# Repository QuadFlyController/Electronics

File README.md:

# QuadFlyController - Flight Controller Hardware

A high-performance, compact, 4-layer flight controller PCB engineered for quadcopters and small UAVs. Built around the STMicroelectronics STM32F411CEU6 MCU, featuring high-rate low-noise motion sensing, barometric altitude tracking, robust power management with dual-source automatic switching, and standard 30.5 mm × 30.5 mm mounting.

---

## 🚀 Key Specifications

| Subsystem | Component | Description |
| :--- | :--- | :--- |
| **Microcontroller (MCU)** | **STM32F411CEU6** | ARM Cortex-M4 @ 100 MHz, FPU, 512 KB Flash, 128 KB SRAM, external 25 MHz HSE oscillator |
| **Inertial Measurement (IMU)** | **ICM-42688-P** | High-precision 6-axis gyroscope & accelerometer on dedicated high-speed SPI bus with interrupt line |
| **Barometer / Altimeter** | **BMP390** | Ultra-low noise barometric pressure sensor on SPI bus for altitude hold |
| **Switching Regulator (Buck)** | **TPS62933** | High-efficiency 3A synchronous step-down converter providing stable +5V rail from battery |
| **Linear Regulator (LDO)** | **AP2112K-3.3** | Ultra-low dropout, low-noise 600 mA 3.3V LDO for clean MCU and analog sensor rails |
| **Power Path Switching** | **TPS2115A** | Seamless automatic power multiplexer between USB VBUS (+5V) and internal Buck converter (+5V) |
| **Transient Protection** | **SMBJ18A** | Bidirectional TVS diode protection on battery input |
| **USB Protection** | **USBLC6-2SC6** | Ultra-low capacitance ESD protection array on USB D+/D- lines |
| **USB Interface** | **USB Type-C (16-pin)** | Firmware flashing (DFU), telemetry, and configuration interface |
| **ESC Interface** | **JST-SH 8-Pin (1.0 mm)** | Standard 4-in-1 ESC connector (VBAT, GND, Motors 1–4, Current sensing) |

---

## 📐 PCB & Mechanical Specifications

- **Dimensions:** 45.0 mm × 45.0 mm with 3.5 mm corner radius
- **Mounting Hole Pattern:** Standard **30.5 mm × 30.5 mm**, 4.3 mm holes (M4, compatible with anti-vibration silicone grommets down to M3 hardware)
- **Layer Stack:** **4-Layer PCB**
  - **F.Cu (Top Layer):** High-speed signals, component breakout, top ground pour
  - **In1.Cu (Inner Layer 1):** Solid ground reference plane (GND)
  - **In2.Cu (Inner Layer 2):** Power distribution (+5V, +3.3V, +BATT) and cross-layer routing
  - **B.Cu (Bottom Layer):** Bottom ground plane and secondary signal routing
- **3D Mechanical Model:** Full 3D STEP model available in [`FlightController/CAD/FlightController.step`](FlightController/CAD/FlightController.step) for frame integration and enclosure design.

---

## 🔌 Pinout & Connector Definitions

### J3: 8-Pin JST-SH 4-in-1 ESC Connector (`SM08B-SRSS-TB`)

| Pin | Net Name | Function / Description |
| :---: | :--- | :--- |
| **1** | `+BATT` | Raw battery voltage input from ESC / PDB |
| **2** | `GND` | Power and signal ground return |
| **3** | `CUR` | Analog current sensing signal from ESC shunt sensor |
| **4** | `M1` | Motor 1 PWM / DShot signal output (STM32 Timer channel) |
| **5** | `M2` | Motor 2 PWM / DShot signal output (STM32 Timer channel) |
| **6** | `M3` | Motor 3 PWM / DShot signal output (STM32 Timer channel) |
| **7** | `M4` | Motor 4 PWM / DShot signal output (STM32 Timer channel) |
| **8** | `GND` | Ground return |

### External Pads & Test Points

- **UART (TX / RX):** External receiver connection (ELRS, Crossfire, SBUS) or GPS telemetry module.
- **SWD (SWDIO / SWCLK):** Hardware debug and in-circuit flashing with ST-Link or J-Link.
- **BOOT0:** Jumper/pad for STM32 internal ROM system bootloader (DFU mode over USB).
- **Status LEDs:**
  - `D1`: Power indicator
  - `D2`: User / Status LED (connected to STM32 GPIO)

---

## 📂 Repository Structure

```text
Electronics/
├── .gitignore                                 # Git ignore configuration
├── LICENSE                                    # License file
├── README.md                                  # Hardware documentation
├── FlightController_Schematic.pdf             # Exported full schematic PDF
│
└── FlightController/                          # KiCad 10 Project Directory
    ├── FlightController.kicad_pro             # KiCad project file
    ├── FlightController.kicad_pcb             # KiCad 4-layer PCB layout
    ├── FlightController.kicad_sch             # Root schematic sheet
    ├── MCU.kicad_sch                          # STM32F411CEU6 microcontroller sheet
    ├── IMU.kicad_sch                          # ICM-42688-P & BMP390 sensor sheet
    ├── PowerManagement.kicad_sch              # Power rails, buck, LDO, & USB sheet
    ├── fp-lib-table                           # Footprint library table
    ├── sym-lib-table                          # Symbol library table
    ├── fabrication-toolkit-options.json       # Production generation settings
    │
    ├── CAD/                                   # 3D Mechanical Models
    │   └── FlightController.step              # Complete 3D STEP assembly of the PCB
    │
    └── production/                            # Manufacturing & Assembly Files
        ├── FlightController.zip               # Gerbers & Drill archive (RS-274X / Excellon)
        ├── bom.csv                            # Bill of Materials (with LCSC part numbers)
        ├── positions.csv                      # Pick-and-Place (CPL) centroid coordinates
        ├── designators.csv                    # Component designator mapping
        └── netlist.ipc                        # IPC-D-356 netlist for bare-board testing
```

---

## 🏭 Manufacturing & Assembly (PCBA)

The files in [`FlightController/production/`](FlightController/production/) are pre-configured and formatted for rapid quoting and ordering with PCB manufacturers (such as JLCPCB, PCBWay, etc.):

1. **PCB Fabrication (Gerber & Drill):**
   - Upload [`FlightController/production/FlightController.zip`](FlightController/production/FlightController.zip).
   - Layers: **4 Layers**
   - Dimensions: **45 mm × 45 mm**
2. **SMT Assembly (PCBA):**
   - **BOM File:** Upload [`FlightController/production/bom.csv`](FlightController/production/bom.csv) (includes pre-matched LCSC part numbers for automated component sourcing).
   - **CPL / Centroid File:** Upload [`FlightController/production/positions.csv`](FlightController/production/positions.csv).
3. **Bare-Board Electrical Test:**
   - [`FlightController/production/netlist.ipc`](FlightController/production/netlist.ipc) is provided for automated flying-probe netlist verification.

---

## 🛠️ Design & Development Environment

- **EDA Software:** [KiCad EDA v10.x](https://www.kicad.org/)
- **To Open the Project:** Launch KiCad and open [`FlightController/FlightController.kicad_pro`](FlightController/FlightController.kicad_pro).
- **Viewing the Schematic without KiCad:** Open [`FlightController_Schematic.pdf`](FlightController_Schematic.pdf).

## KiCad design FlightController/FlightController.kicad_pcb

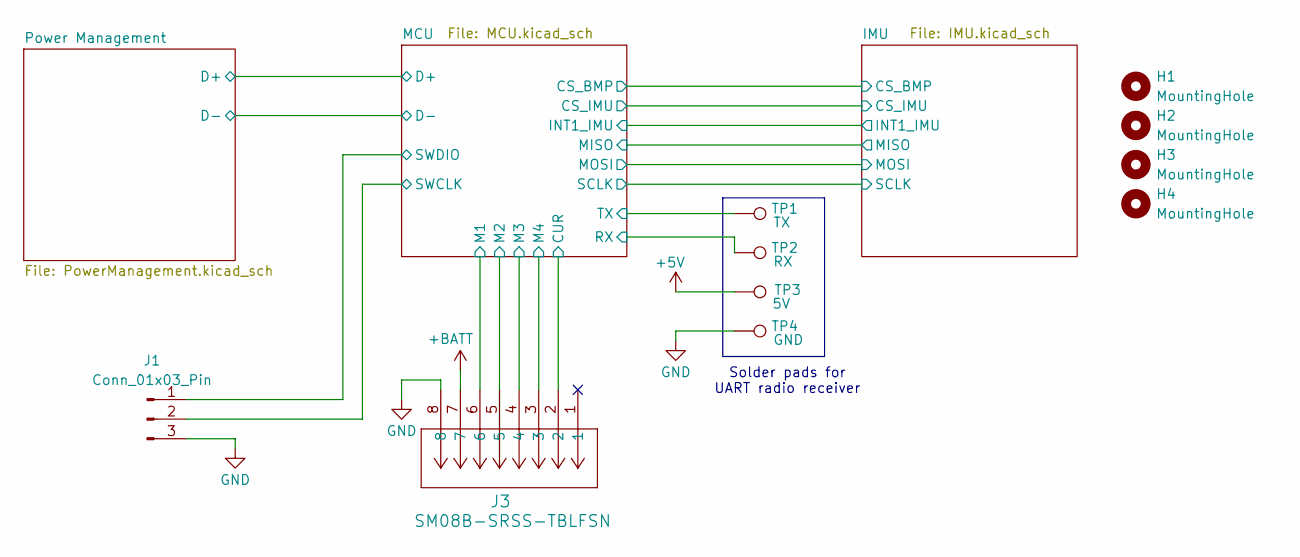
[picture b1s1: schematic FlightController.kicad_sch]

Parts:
H1, H2, H3, H4: MountingHole; MountingHole_4.3mm_M4
J1: Conn_01x03_Pin; PinHeader_1x03_P1.00mm_Vertical
J3: SM08B-SRSS-TBLFSN; XY-SM08B-SRSS-TB; LCSC C54582896
TP1: TX; TestPoint_Pad_3.0x3.0mm
TP2: RX; TestPoint_Pad_3.0x3.0mm
TP3: 5V; TestPoint_Pad_3.0x3.0mm
TP4: GND; TestPoint_Pad_3.0x3.0mm

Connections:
+5V: TP3.1 (1_1); also elsewhere on the board
+BATT: J3.7; also elsewhere on the board
/MCU/CUR: J3.2; also elsewhere on the board
/MCU/M1: J3.6; also elsewhere on the board
/MCU/M2: J3.5; also elsewhere on the board
/MCU/M3: J3.4; also elsewhere on the board
/MCU/M4: J3.3; also elsewhere on the board
/MCU/RX: TP2.1 (1_1); also elsewhere on the board
/MCU/SWCLK: J1.2; also elsewhere on the board
/MCU/SWDIO: J1.1; also elsewhere on the board
/MCU/TX: TP1.1 (1_1); also elsewhere on the board
GND: J1.3, J3.8, TP4.1 (1_1); also elsewhere on the board

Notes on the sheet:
Solder pads for UART radio receiver

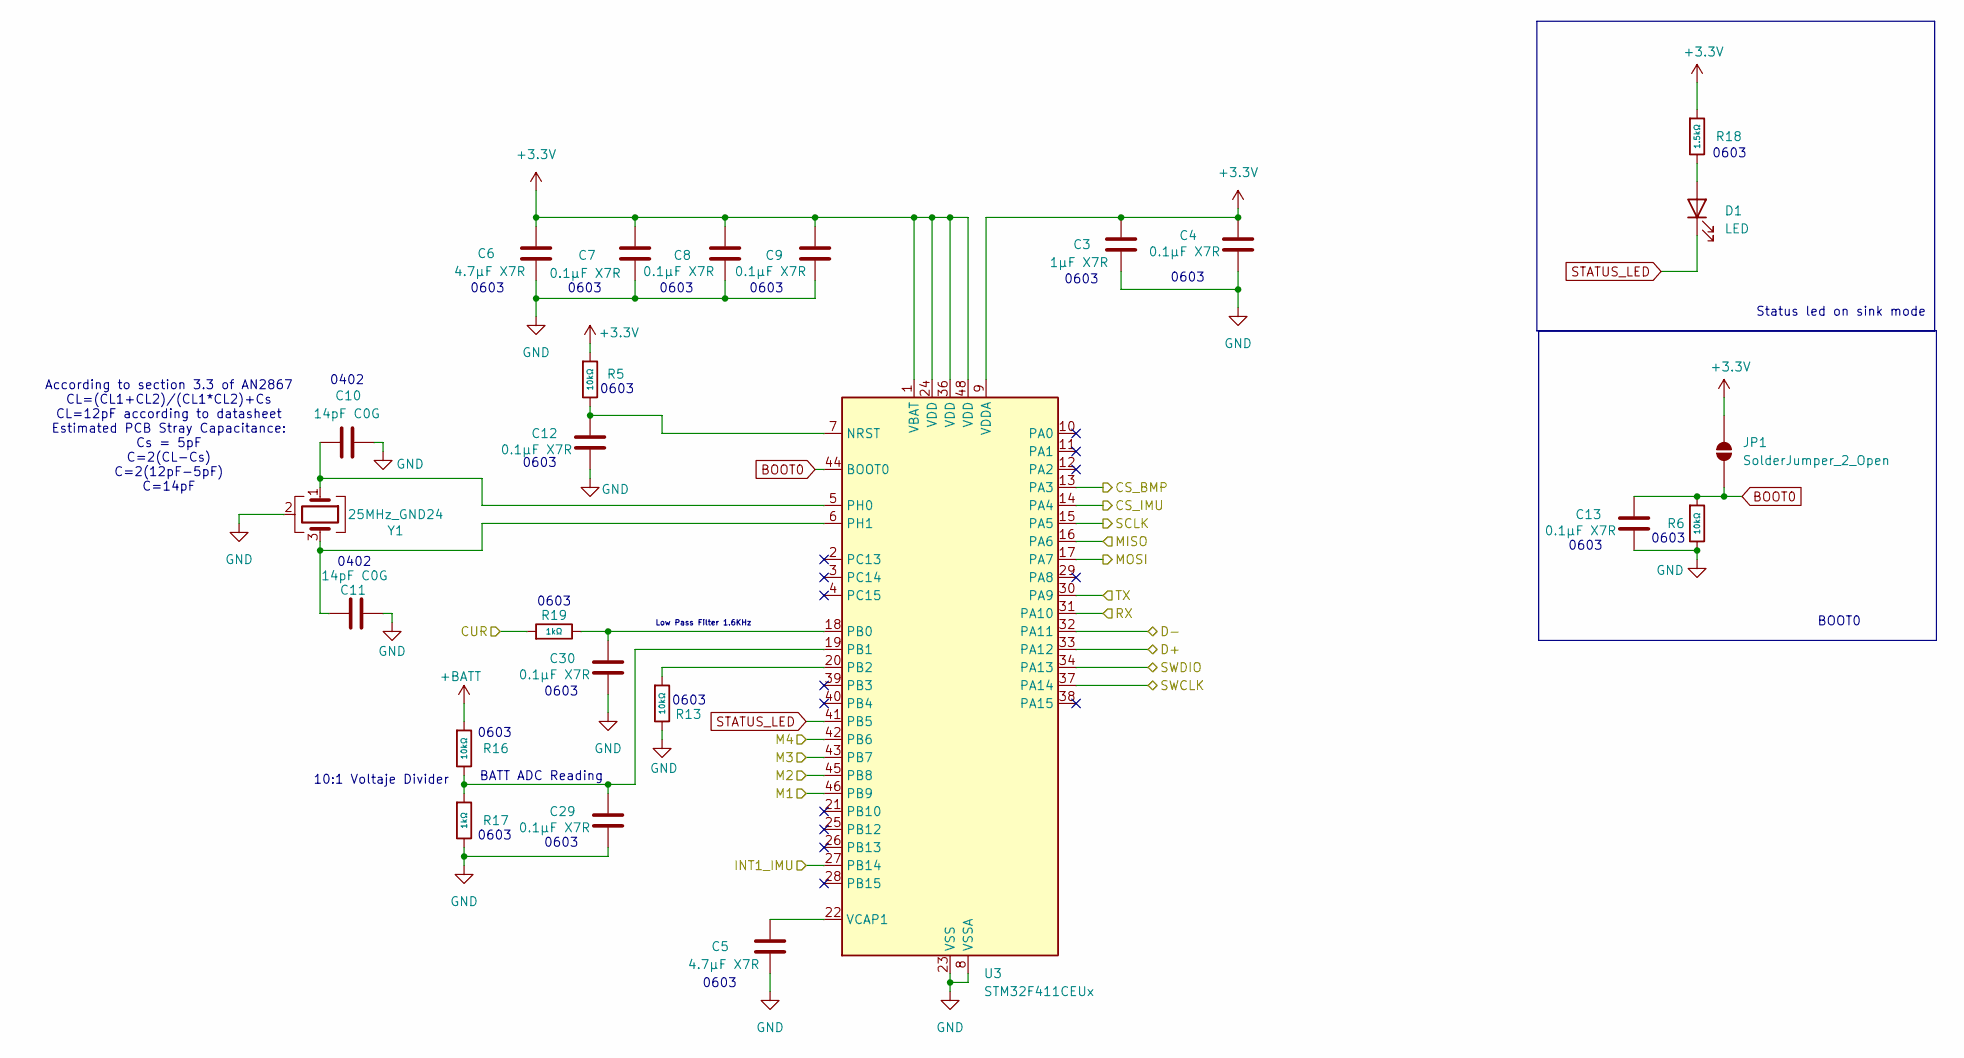
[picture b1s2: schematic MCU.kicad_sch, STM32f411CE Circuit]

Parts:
C3: 1μF X7R; C_0603_1608Metric_Pad1.08x0.95mm_HandSolder; LCSC C5199872
C4, C7, C8, C9, C12, C13, C29, C30: 0.1μF X7R; C_0603_1608Metric_Pad1.08x0.95mm_HandSolder; LCSC C1590
C5, C6: 4.7μF X7R; C_0603_1608Metric_Pad1.08x0.95mm_HandSolder; LCSC C6119822
C10, C11: 14pF C0G; C_0402_1005Metric_Pad0.74x0.62mm_HandSolder; LCSC C5360816
D1: LED; LED_0603_1608Metric; LCSC C2286
JP1: SolderJumper_2_Open; SolderJumper-2_P1.3mm_Open_Pad1.0x1.5mm
R5, R6, R13, R16: 10kΩ; R_0603; Overload Voltage (Max) 75V; Tolerance ±1%; Part 0603WAF1002T5E; LCSC C25804
R17, R19: 1kΩ; R_0603; Overload Voltage (Max) 75V; Tolerance ±1%; Part 0603WAF1001T5E; LCSC C21190
R18: 1.5kΩ; R_0603; Overload Voltage (Max) 75V; Tolerance ±1%; Part 0603WAF1501T5E; LCSC C22843
U3: STM32F411CEUx; QFN-48-1EP_7x7mm_P0.5mm_EP5.6x5.6mm
Y1: 25MHz_GND24; CRYSTAL-SMD_4P-L3.2-W2.5-BL; LCSC C9006

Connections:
+3.3V: C3.1, C4.1, C6.1, C7.1, C8.1, C9.1, JP1.2 (B), R5.1, R18.1, U3.1 (VBAT), U3.9 (VDDA), U3.24 (VDD), U3.36 (VDD), U3.48 (VDD); also elsewhere on the board
+BATT: R16.1; also elsewhere on the board
/IMU/CS_BMP: U3.13 (PA3); also elsewhere on the board
/IMU/CS_IMU: U3.14 (PA4); also elsewhere on the board
/IMU/INT1_IMU: U3.27 (PB14); also elsewhere on the board
/IMU/MISO: U3.16 (PA6); also elsewhere on the board
/IMU/MOSI: U3.17 (PA7); also elsewhere on the board
/IMU/SCLK: U3.15 (PA5); also elsewhere on the board
/MCU/CUR: R19.1; also elsewhere on the board
/MCU/D+: U3.33 (PA12); also elsewhere on the board
/MCU/D-: U3.32 (PA11); also elsewhere on the board
/MCU/M1: U3.46 (PB9); also elsewhere on the board
/MCU/M2: U3.45 (PB8); also elsewhere on the board
/MCU/M3: U3.43 (PB7); also elsewhere on the board
/MCU/M4: U3.42 (PB6); also elsewhere on the board
/MCU/RX: U3.31 (PA10); also elsewhere on the board
/MCU/SWCLK: U3.37 (PA14); also elsewhere on the board
/MCU/SWDIO: U3.34 (PA13); also elsewhere on the board
/MCU/TX: U3.30 (PA9); also elsewhere on the board
BOOT0: C13.1, JP1.1 (A), R6.1, U3.44 (BOOT0)
GND: C3.2, C4.2, C5.2, C6.2, C7.2, C8.2, C9.2, C10.1, C11.2, C12.2, C13.2, C29.2, C30.2, R6.2, R13.2, R17.2, U3.8 (VSSA), U3.23 (VSS), U3.35 (VSS), U3.47 (VSS), U3.49 (VSS), Y1.2 (G), Y1.4 (G); also elsewhere on the board
unnamed: D1.2 (A), R18.2
unnamed: C12.1, R5.2, U3.7 (NRST)
unnamed: C30.1, R19.2, U3.18 (PB0)
unnamed: C29.1, R16.2, R17.1, U3.19 (PB1)
unnamed: R13.1, U3.20 (PB2)
unnamed: C10.2, U3.5 (PH0), Y1.1
unnamed: C11.1, U3.6 (PH1), Y1.3
unnamed: C5.1, U3.22 (VCAP1)
STATUS_LED: D1.1 (K), U3.41 (PB5)

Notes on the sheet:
0603
BOOT0
BATT ADC Reading
Status led on sink mode
0402
Low Pass Filter 1.6KHz
10:1 Voltaje Divider
According to section 3.3 of AN2867 CL=(CL1+CL2)/(CL1*CL2)+Cs CL=12pF according to datasheet Estimated PCB Stray Capacitance: Cs = 5pF C=2(CL-Cs) C=2(12pF-5pF) C=14pF

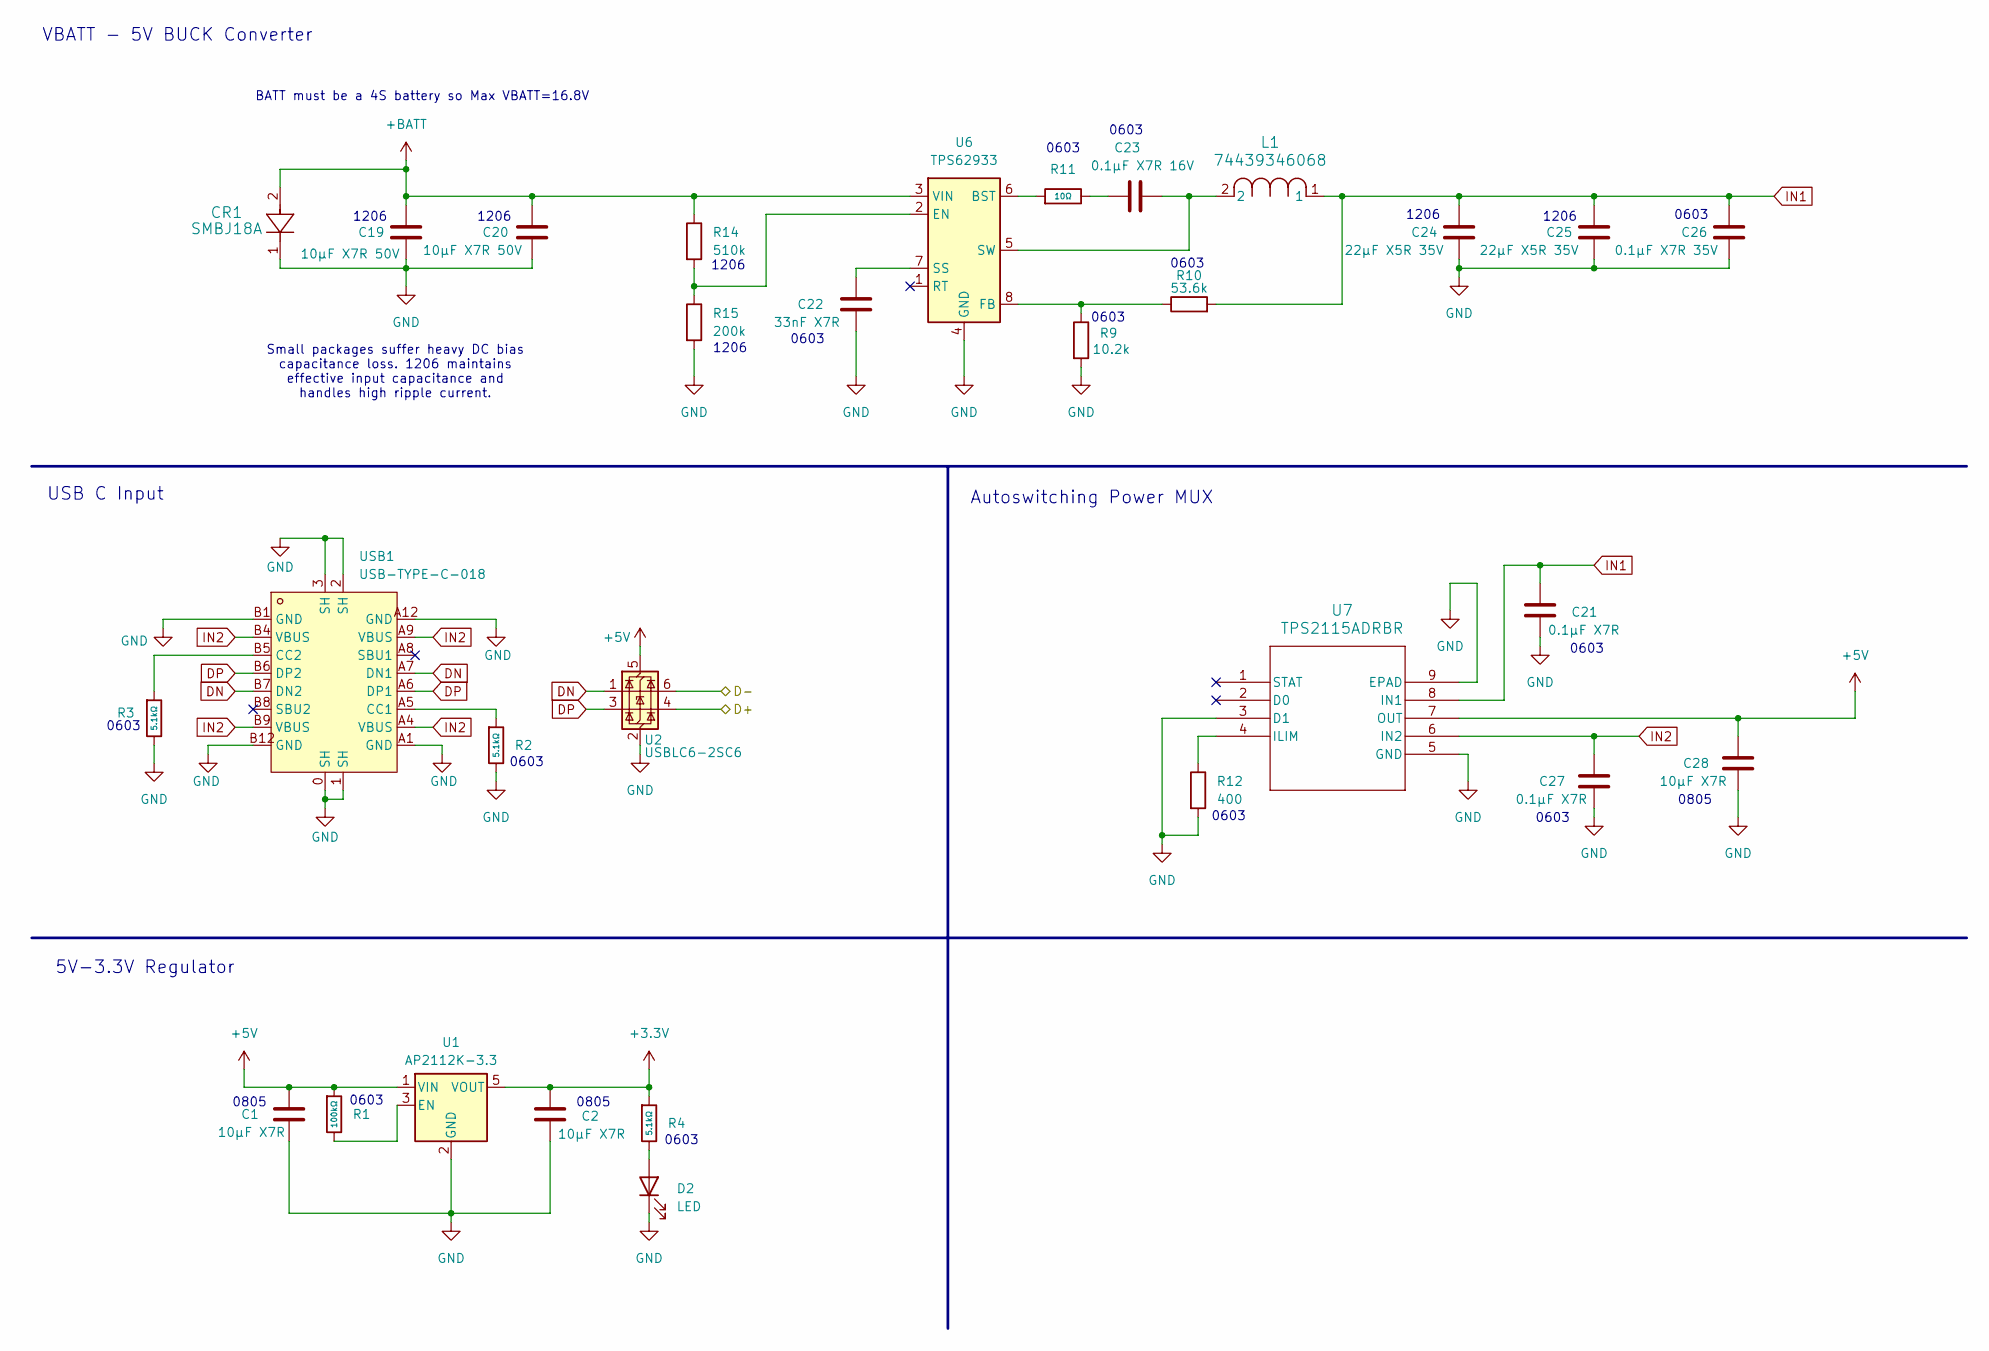
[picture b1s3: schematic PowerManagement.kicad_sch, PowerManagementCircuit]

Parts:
C1, C2, C28: 10μF X7R; C_0805_2012Metric_Pad1.18x1.45mm_HandSolder; LCSC C326595
C19, C20: 10μF X7R 50V; C_1206_3216Metric_Pad1.33x1.80mm_HandSolder; LCSC C89632
C21, C27: 0.1μF X7R; C_0603_1608Metric_Pad1.08x0.95mm_HandSolder; LCSC C1590
C22: 33nF X7R; C_0603_1608Metric_Pad1.08x0.95mm_HandSolder; LCSC C1614
C23: 0.1μF X7R 16V; C_0603_1608Metric_Pad1.08x0.95mm_HandSolder; LCSC C1590
C24, C25: 22μF X5R 35V; C_1206_3216Metric_Pad1.33x1.80mm_HandSolder; LCSC C342620
C26: 0.1μF X7R 35V; C_0603_1608Metric_Pad1.08x0.95mm_HandSolder; LCSC C385964
CR1: SMBJ18A; LCSC C10212
D2: LED; LED_0603_1608Metric; LCSC C2286
L1: 74439346068; LCSC C2041388
R1: 100kΩ; R_0603; Overload Voltage (Max) 75V; Tolerance ±1%; Part 0603WAF1003T5E; LCSC C25803
R2, R3, R4: 5.1kΩ; R_0603; Overload Voltage (Max) 75V; Tolerance ±1%; Part 0603WAF5101T5E; LCSC C23186
R9: 10.2k; R_0603_1608Metric_Pad0.98x0.95mm_HandSolder; LCSC C22772
R10: 53.6k; R_0603_1608Metric_Pad0.98x0.95mm_HandSolder; LCSC C23074
R11: 10Ω; R_0603; Overload Voltage (Max) 75V; Tolerance ±1%; Part 0603WAF100JT5E; LCSC C22859
R12: 400; R_0603_1608Metric_Pad0.98x0.95mm_HandSolder; LCSC C5841024
R14: 510k; R_1206_3216Metric_Pad1.30x1.75mm_HandSolder; LCSC C2774961
R15: 200k; R_1206_3216Metric_Pad1.30x1.75mm_HandSolder; LCSC C5720887
U1: AP2112K-3.3; SOT-23-5_HandSoldering; LCSC C23380830
U2: USBLC6-2SC6; SOT-23-6_Handsoldering; LCSC C7519
U6: TPS62933; SOT-583-8; LCSC C3200405
U7: TPS2115ADRBR; LCSC C140321
USB1: USB-TYPE-C-018; USB-C_SMD-TYPE-C-31-M-12; MPN USB-TYPE-C-018; LCSC Part C2927038

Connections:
+3.3V: C2.1, R4.1, U1.5 (VOUT); also elsewhere on the board
+5V: C1.1, C28.1, R1.1, U1.1 (VIN), U2.5 (VBUS), U7.7 (OUT); also elsewhere on the board
+BATT: C19.1, C20.1, CR1.2, R14.1, U6.3 (VIN); also elsewhere on the board
/MCU/D+: U2.4 (I/O2); also elsewhere on the board
/MCU/D-: U2.6 (I/O1); also elsewhere on the board
DN: U2.1 (I/O1), USB1.A7 (DN1), USB1.B7 (DN2)
DP: U2.3 (I/O2), USB1.A6 (DP1), USB1.B6 (DP2)
GND: C1.2, C2.2, C19.2, C20.2, C21.2, C22.2, C24.2, C25.2, C26.2, C27.2, C28.2, CR1.1, D2.1 (K), R2.2, R3.2, R9.2, R12.2, R15.2, U1.2 (GND), U2.2 (GND), U6.4 (GND), U7.3 (D1), U7.5 (GND), U7.9 (EPAD), USB1.0 (SH), USB1.1 (SH), USB1.2 (SH), USB1.3 (SH), USB1.A1 (GND), USB1.A12 (GND), USB1.B1 (GND), USB1.B12 (GND); also elsewhere on the board
IN1: C21.1, C24.1, C25.1, C26.1, L1.1, R10.2, U7.8 (IN1)
IN2: C27.1, U7.6 (IN2), USB1.A4 (VBUS), USB1.A9 (VBUS), USB1.B4 (VBUS), USB1.B9 (VBUS)
unnamed: C23.2, R11.2
unnamed: D2.2 (A), R4.2
unnamed: R1.2, U1.3 (EN)
unnamed: R11.1, U6.6 (BST)
unnamed: R14.2, R15.1, U6.2 (EN)
unnamed: R9.1, R10.1, U6.8 (FB)
unnamed: C22.1, U6.7 (SS)
unnamed: C23.1, L1.2, U6.5 (SW)
unnamed: R12.1, U7.4 (ILIM)
unnamed: R2.1, USB1.A5 (CC1)
unnamed: R3.1, USB1.B5 (CC2)

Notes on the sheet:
0603
Small packages suffer heavy DC bias capacitance loss. 1206 maintains effective input capacitance and handles high ripple current.
0805
Autoswitching Power MUX
1206
VBATT - 5V BUCK Converter
USB C Input
BATT must be a 4S battery so Max VBATT=16.8V
5V-3.3V Regulator

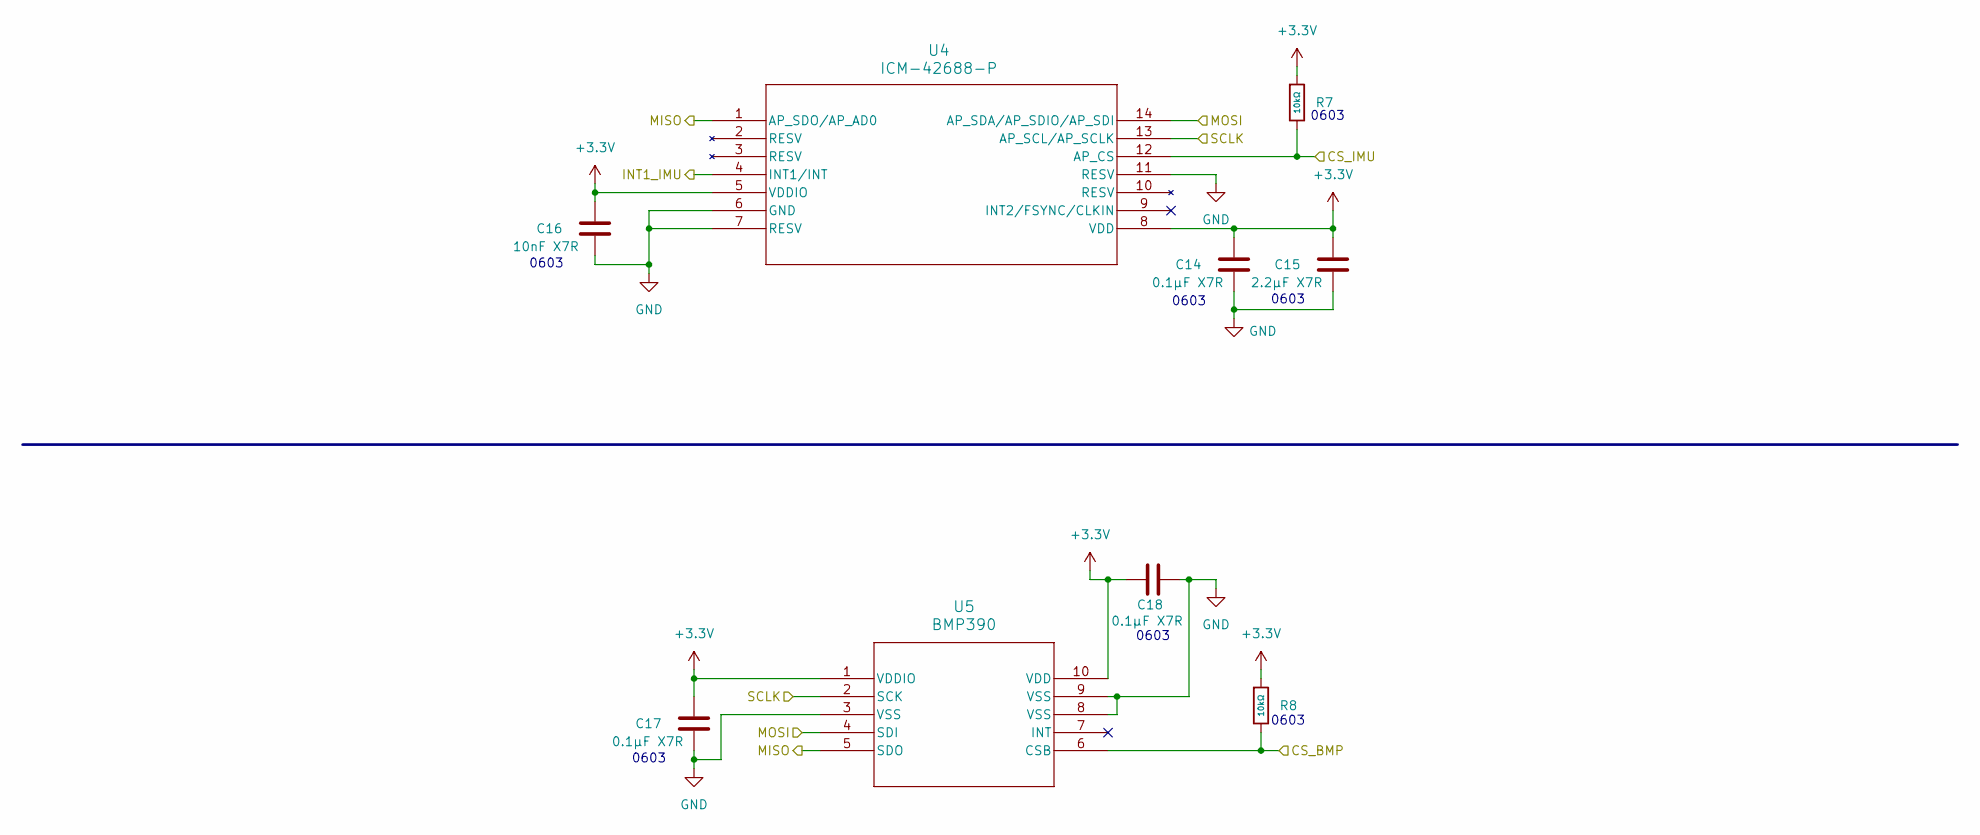
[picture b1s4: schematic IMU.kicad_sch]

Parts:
C14, C17, C18: 0.1μF X7R; C_0603_1608Metric_Pad1.08x0.95mm_HandSolder; LCSC C1590
C15: 2.2μF X7R; C_0603_1608Metric_Pad1.08x0.95mm_HandSolder; LCSC C43922
C16: 10nF X7R; C_0603_1608Metric_Pad1.08x0.95mm_HandSolder; LCSC C1589
R7, R8: 10kΩ; R_0603; Overload Voltage (Max) 75V; Tolerance ±1%; Part 0603WAF1002T5E; LCSC C25804
U4: ICM-42688-P; ICM-42688-P-M
U5: BMP390

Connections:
+3.3V: C14.1, C15.1, C16.1, C17.1, C18.1, R7.1, R8.1, U4.5 (VDDIO), U4.8 (VDD), U5.1 (VDDIO), U5.10 (VDD); also elsewhere on the board
/IMU/CS_BMP: R8.2, U5.6 (CSB); also elsewhere on the board
/IMU/CS_IMU: R7.2, U4.12 (AP_CS); also elsewhere on the board
/IMU/INT1_IMU: U4.4 (INT1/INT); also elsewhere on the board
/IMU/MISO: U4.1 (AP_SDO/AP_AD0), U5.5 (SDO); also elsewhere on the board
/IMU/MOSI: U4.14 (AP_SDA/AP_SDIO/AP_SDI), U5.4 (SDI); also elsewhere on the board
/IMU/SCLK: U4.13 (AP_SCL/AP_SCLK), U5.2 (SCK); also elsewhere on the board
GND: C14.2, C15.2, C16.2, C17.2, C18.2, U4.6 (GND), U4.7 (RESV), U4.11 (RESV), U5.3 (VSS), U5.8 (VSS), U5.9 (VSS); also elsewhere on the board

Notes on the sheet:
0603

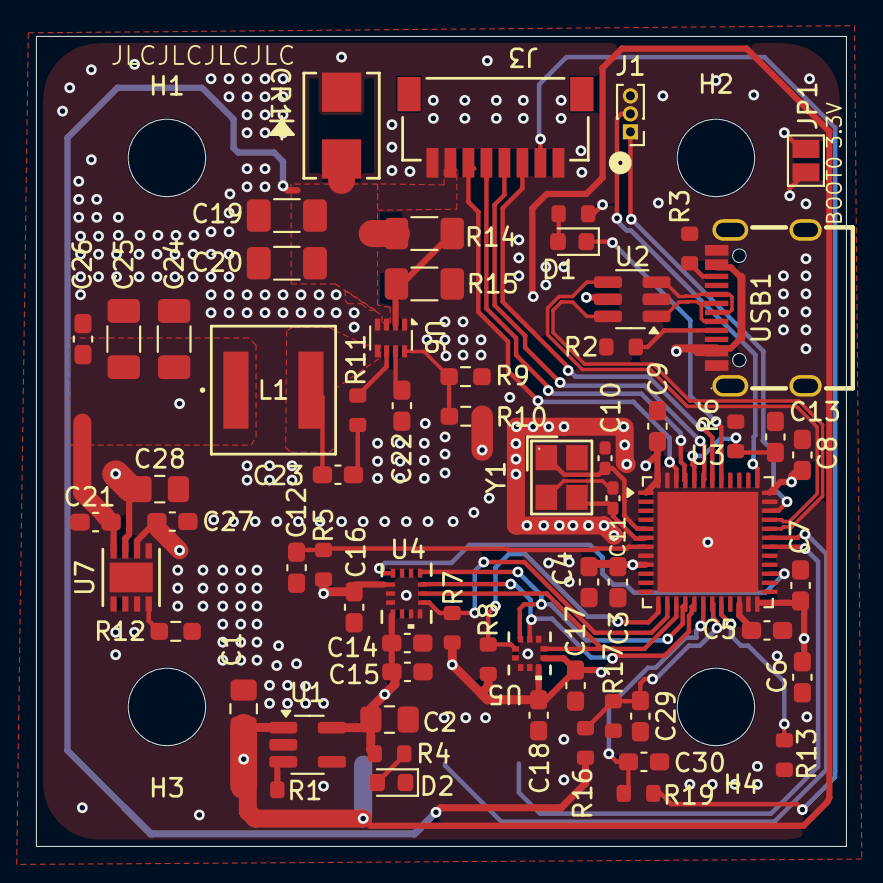
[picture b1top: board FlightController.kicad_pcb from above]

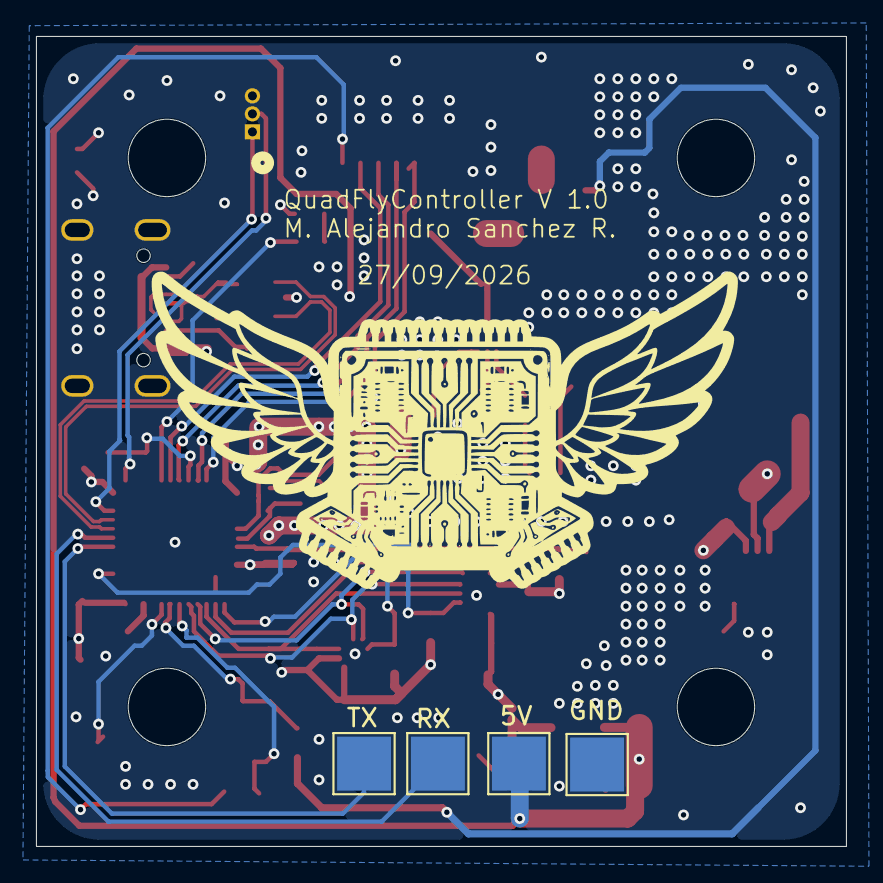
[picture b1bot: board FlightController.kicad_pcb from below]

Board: 4 copper layers, 45.0 x 45.0 mm, 73 parts (4 on the bottom side), 46 nets.

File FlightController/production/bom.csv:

Designator,Footprint,Quantity,Value,LCSC Part #
"C1, C2, C28",0805,3,10μF X7R,C326595
"C10, C11",0402,2,14pF C0G,C5360816
"C12, C13, C14, C17, C18, C21, C27, C29, C30, C4, C7, C8, C9",0603,13,0.1μF X7R,C1590
C15,0603,1,2.2μF X7R,C43922
C16,0603,1,10nF X7R,C1589
"C19, C20",1206,2,10μF X7R 50V,C89632
C22,0603,1,33nF X7R,C1614
C23,0603,1,0.1μF X7R 16V,C1590
"C24, C25",1206,2,22μF X5R 35V,C342620
C26,0603,1,0.1μF X7R 35V,C385964
C3,0603,1,1μF X7R,C5199872
"C5, C6",0603,2,4.7μF X7R,C6119822
CR1,SMBJ18A,1,SMBJ18A,C10212
"D1, D2",0603,2,LED,C2286
J3,XY-SM08B-SRSS-TB,1,SM08B-SRSS-TBLFSN,C54582896
L1,74439346068,1,74439346068,C2041388
R1,R_0603,1,100kΩ,C25803
R10,0603,1,53.6k,C23074
R11,R_0603,1,10Ω,C22859
R12,0603,1,400,C5841024
"R13, R16, R5, R6, R7, R8",R_0603,6,10kΩ,C25804
R14,1206,1,510k,C2774961
R15,1206,1,200k,C5720887
"R17, R19",R_0603,2,1kΩ,C21190
R18,R_0603,1,1.5kΩ,C22843
"R2, R3, R4",R_0603,3,5.1kΩ,C23186
R9,0603,1,10.2k,C22772
U1,SOT-23-5_HandSoldering,1,AP2112K-3.3,C23380830
U2,SOT-23-6_Handsoldering,1,USBLC6-2SC6,C7519
U6,SOT-583-8,1,TPS62933,C3200405
U7,TPS2115ADRBR,1,TPS2115ADRBR,C140321
USB1,USB-C_SMD-TYPE-C-31-M-12,1,USB-TYPE-C-018,C2927038
Y1,CRYSTAL-SMD_4P-L3.2-W2.5-BL,1,25MHz_GND24,C9006
